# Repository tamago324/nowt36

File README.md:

# nowt36

以下の特徴を持ったキーボードです。

* 自然と手が置ける配列
* 一体型だけど分割型
* 片手5列
* ホットスワップ対応
* ミドルアクリルプレート対応 (オプション)
* アンダーグロー対応 (オプション)

## LICENSE

<br />この 作品 は <a rel="license" href="http://creativecommons.org/licenses/by/4.0/">クリエイティブ・コモンズ 表示 4.0 国際 ライセンス</a>の下に提供されています。

> 帰属—適切なクレジットを表示し、ライセンスへのリンクを提供し、変更が行われたかどうかを示す必要があります。

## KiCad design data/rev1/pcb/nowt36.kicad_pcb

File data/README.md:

# data

| ディレクトリ                      | 説明                                                                      |
|-----------------------------------|---------------------------------------------------------------------------|
| `pcb/`                            | メインPCB                                                                 |
| `pcb_promicro_plate/`             | ProMicro保護プレート用 KiCad プロジェクトたち                             |
| `pcb_top_plate/`                  | トッププレート用 KiCad プロジェクト                                       |
| `dxf/`                            | DXFファイル                                                               |
| `svg/`                            | プレートに使用できるSVGファイル                                           |
| `nowt.FCStd`                      | プレートなどのデータを生成するときに使用したFreeCADプロジェクト           |
| `bk_pcb_middle_plate_lower_data/` | ミドルアクリルプレート (下) 作成用 KiCadプロジェクト (発注には使用しない) |

## 発注する場合

### PCB

| パーツ               | 発注時に使用するファイル                                                                       |
|----------------------|------------------------------------------------------------------------------------------------|
| メインPCB            | `pcb/gerber_to_order` 内の対象の業者のzipファイル                                              |
| ProMicro保護プレート | `pcb_promicro_plate/` の中から発注したいプレートの gerber_to_order 内の対象の業者のzipファイル |
| トッププレート       | `pcb_top_plate/gerber_to_order` 内の対象の業者のzipファイル                                    |

### アクリルプレート

#### それぞれのアクリルプレートのデータを自分で加工して、発注する場合

| パーツ                 | ファイル名                   | 備考                                     |
|------------------------|------------------------------|------------------------------------------|
| ボトムプレート         | `svg/bottom.svg`             |                                          |
| ミドルプレート (上)    | `svg/middle_upper.svg`       |                                          |
| ミドルプレート (下)    | `svg/middle_lower.svg.svg`   |                                          |
| ミドルプレート (上) 左 | `svg/middle_upper_left.svg`  | ミドルプレート (上) を左右で分割したもの |
| ミドルプレート (上) 右 | `svg/middle_upper_right.svg` | ミドルプレート (上) を左右で分割したもの |

ミドルプレート (上) 左、ミドルプレート (上) 右 は、A4サイズの中に「ミドルプレート (下)」、「ミドルプレート (上) 右」、「ミドルプレート (上) 左」 を含めたいときに使用できます。

#### Elecrow などにすべてのアクリルプレートを発注する場合 (DXFファイル)

| パーツ                                                                  | ファイル名                            |
|-------------------------------------------------------------------------|---------------------------------------|
| ボトムプレート、ミドルプレート (上)、ミドルプレート (下) を含んだデータ | `dxf/313x255_bottom_middle_plate.dxf` |

### シリコンカットシート

| パーツ                 | ファイル名                  |
|------------------------|-----------------------------|
| シリコンカット用シート | `svg/silicon_cut_sheet.svg` |

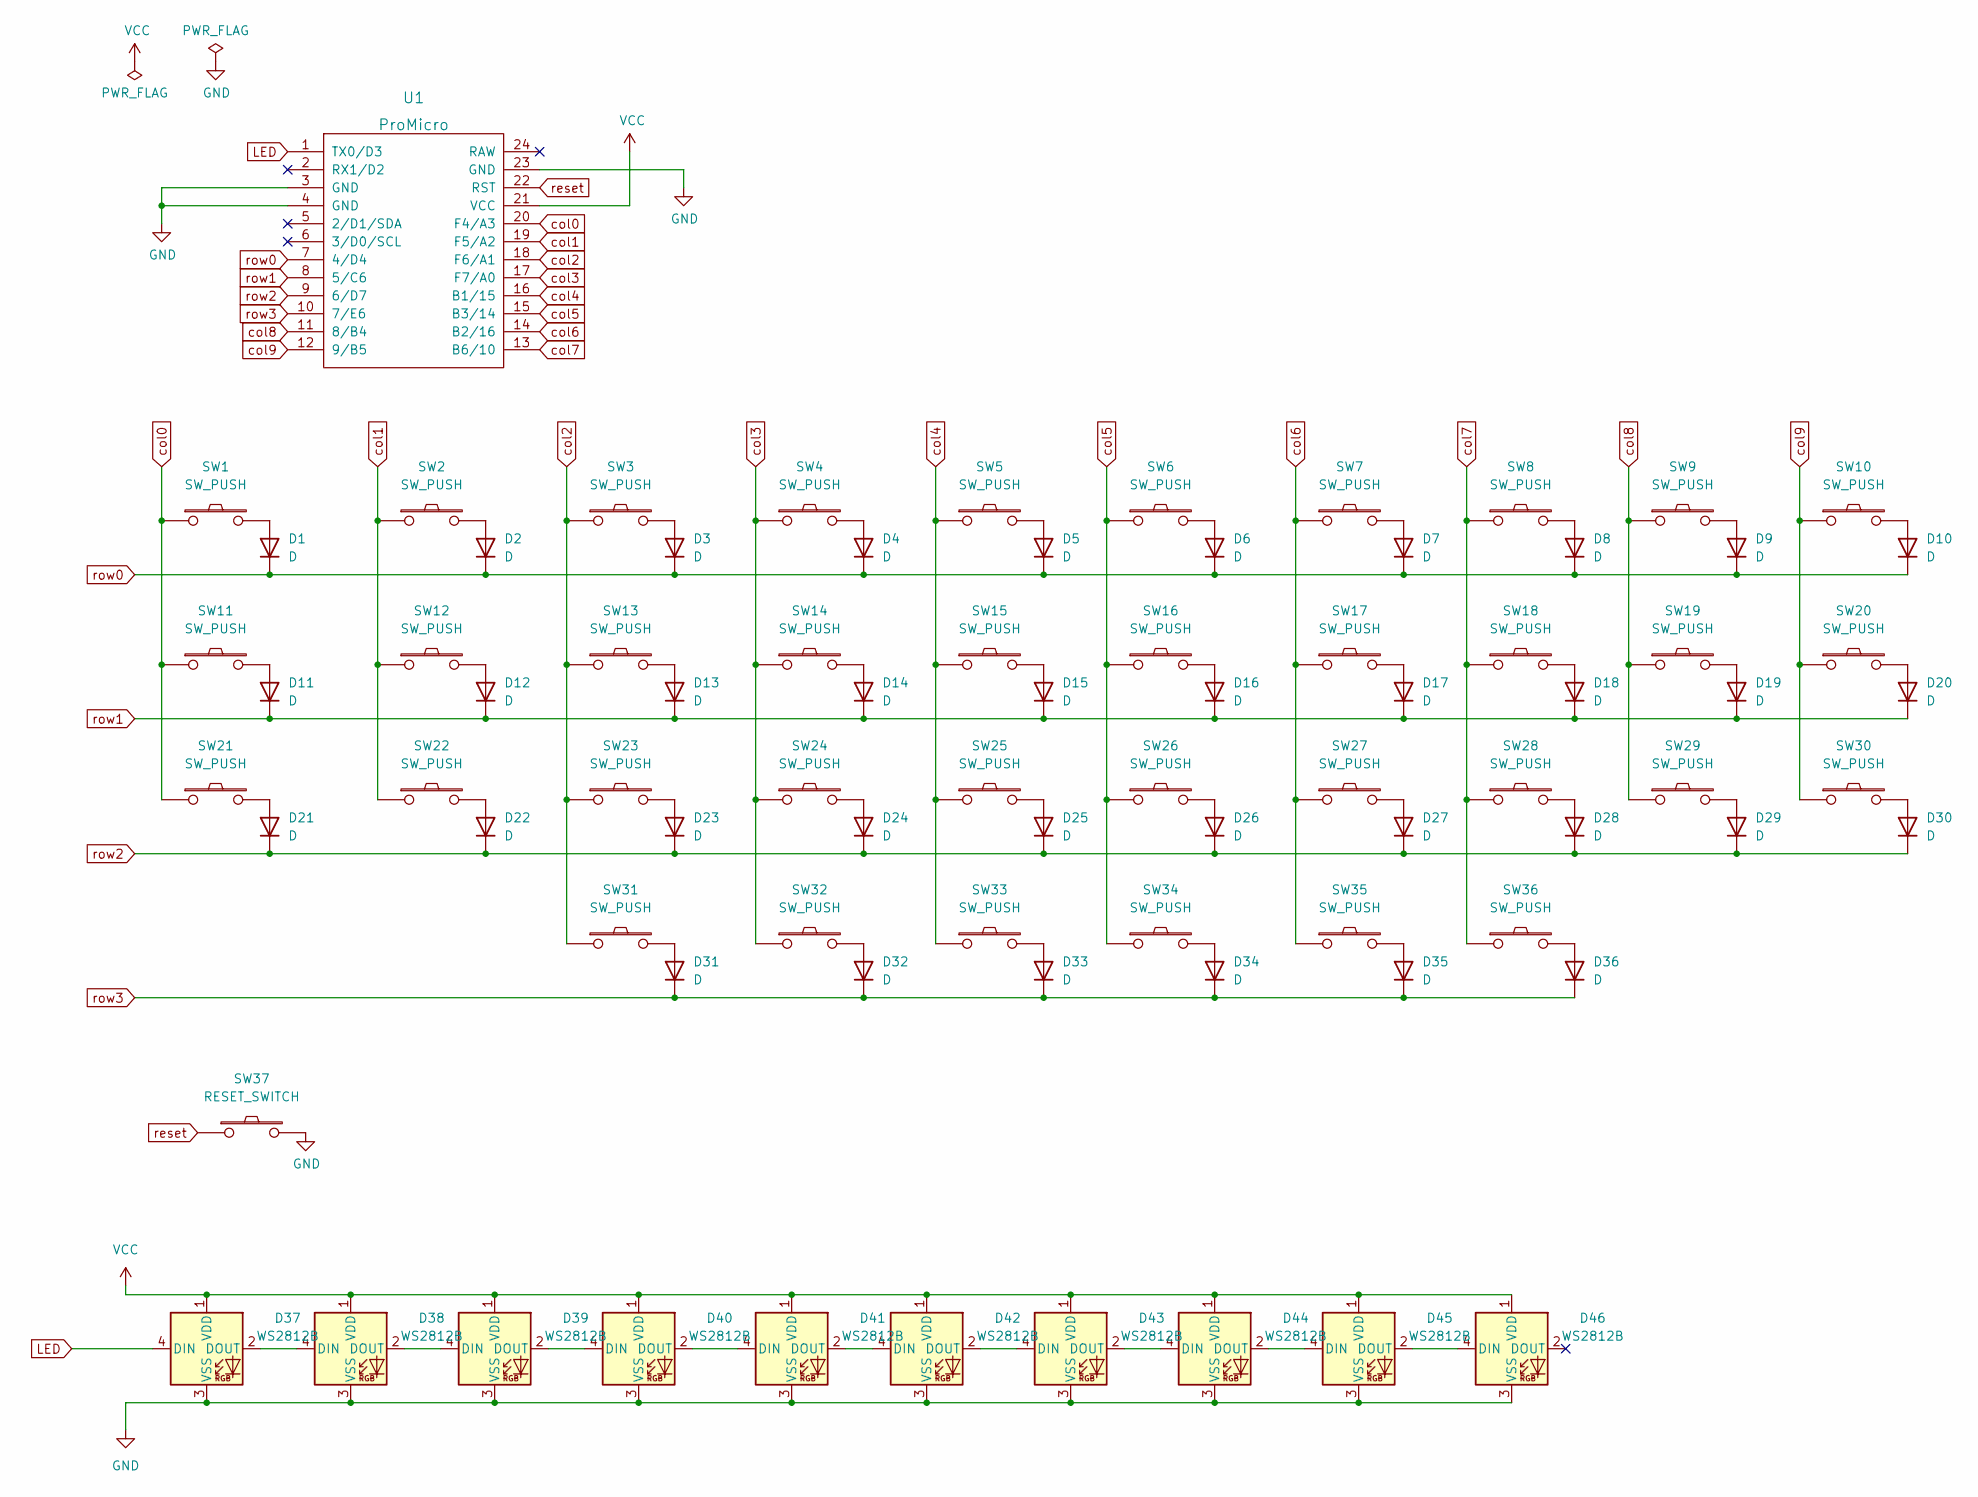
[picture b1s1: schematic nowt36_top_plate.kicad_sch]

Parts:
D1, D2, D3, D4, D5, D6, D7, D8, D9, D10, D11, D12, D13, D14, D15, D16, D17, D18, D19, D20, D21, D22, D23, D24, D25, D26, D27, D28, D29, D30, D31, D32, D33, D34, D35, D36: D; Diode_SMD
D37, D38, D39, D40, D41, D42, D43, D44, D45, D46: WS2812B; LED_WS2812B_PLCC4_5.0x5.0mm_P3.2mm_Back
SW1, SW2, SW3, SW4, SW5, SW6, SW7, SW8, SW9, SW10, SW11, SW12, SW13, SW14, SW15, SW16, SW17, SW18, SW19, SW20, SW21, SW22, SW23, SW24, SW25, SW26, SW27, SW28, SW29, SW30, SW31, SW32, SW33, SW34, SW35, SW36: SW_PUSH; CherryMX_Hotswap
SW37: RESET_SWITCH; ResetSW_1side_back
U1: ProMicro; ProMicro_v3.5_mods

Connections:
GND: D37.3 (VSS), D38.3 (VSS), D39.3 (VSS), D40.3 (VSS), D41.3 (VSS), D42.3 (VSS), D43.3 (VSS), D44.3 (VSS), D45.3 (VSS), D46.3 (VSS), SW37.2, U1.3 (GND), U1.4 (GND), U1.23 (GND)
LED: D37.4 (DIN), U1.1 (TX0/D3)
unnamed: D1.2 (A), SW1.2
unnamed: D2.2 (A), SW2.2
unnamed: D3.2 (A), SW3.2
unnamed: D4.2 (A), SW4.2
unnamed: D5.2 (A), SW5.2
unnamed: D6.2 (A), SW6.2
unnamed: D7.2 (A), SW7.2
unnamed: D8.2 (A), SW8.2
unnamed: D9.2 (A), SW9.2
unnamed: D10.2 (A), SW10.2
unnamed: D11.2 (A), SW11.2
unnamed: D12.2 (A), SW12.2
unnamed: D13.2 (A), SW13.2
unnamed: D14.2 (A), SW14.2
unnamed: D15.2 (A), SW15.2
unnamed: D16.2 (A), SW16.2
unnamed: D17.2 (A), SW17.2
unnamed: D18.2 (A), SW18.2
unnamed: D19.2 (A), SW19.2
unnamed: D20.2 (A), SW20.2
unnamed: D21.2 (A), SW21.2
unnamed: D22.2 (A), SW22.2
unnamed: D23.2 (A), SW23.2
unnamed: D24.2 (A), SW24.2
unnamed: D25.2 (A), SW25.2
unnamed: D26.2 (A), SW26.2
unnamed: D27.2 (A), SW27.2
unnamed: D28.2 (A), SW28.2
unnamed: D29.2 (A), SW29.2
unnamed: D30.2 (A), SW30.2
unnamed: D31.2 (A), SW31.2
unnamed: D32.2 (A), SW32.2
unnamed: D33.2 (A), SW33.2
unnamed: D34.2 (A), SW34.2
unnamed: D35.2 (A), SW35.2
unnamed: D36.2 (A), SW36.2
unnamed: D37.2 (DOUT), D38.4 (DIN)
unnamed: D38.2 (DOUT), D39.4 (DIN)
unnamed: D39.2 (DOUT), D40.4 (DIN)
unnamed: D40.2 (DOUT), D41.4 (DIN)
unnamed: D41.2 (DOUT), D42.4 (DIN)
unnamed: D42.2 (DOUT), D43.4 (DIN)
unnamed: D43.2 (DOUT), D44.4 (DIN)
unnamed: D44.2 (DOUT), D45.4 (DIN)
unnamed: D45.2 (DOUT), D46.4 (DIN)
VCC: D37.1 (VDD), D38.1 (VDD), D39.1 (VDD), D40.1 (VDD), D41.1 (VDD), D42.1 (VDD), D43.1 (VDD), D44.1 (VDD), D45.1 (VDD), D46.1 (VDD), U1.21 (VCC)
col0: SW1.1, SW11.1, SW21.1, U1.20 (F4/A3)
col1: SW2.1, SW12.1, SW22.1, U1.19 (F5/A2)
col2: SW3.1, SW13.1, SW23.1, SW31.1, U1.18 (F6/A1)
col3: SW4.1, SW14.1, SW24.1, SW32.1, U1.17 (F7/A0)
col4: SW5.1, SW15.1, SW25.1, SW33.1, U1.16 (B1/15)
col5: SW6.1, SW16.1, SW26.1, SW34.1, U1.15 (B3/14)
col6: SW7.1, SW17.1, SW27.1, SW35.1, U1.14 (B2/16)
col7: SW8.1, SW18.1, SW28.1, SW36.1, U1.13 (B6/10)
col8: SW9.1, SW19.1, SW29.1, U1.11 (8/B4)
col9: SW10.1, SW20.1, SW30.1, U1.12 (9/B5)
reset: SW37.1, U1.22 (RST)
row0: D1.1 (K), D2.1 (K), D3.1 (K), D4.1 (K), D5.1 (K), D6.1 (K), D7.1 (K), D8.1 (K), D9.1 (K), D10.1 (K), U1.7 (4/D4)
row1: D11.1 (K), D12.1 (K), D13.1 (K), D14.1 (K), D15.1 (K), D16.1 (K), D17.1 (K), D18.1 (K), D19.1 (K), D20.1 (K), U1.8 (5/C6)
row2: D21.1 (K), D22.1 (K), D23.1 (K), D24.1 (K), D25.1 (K), D26.1 (K), D27.1 (K), D28.1 (K), D29.1 (K), D30.1 (K), U1.9 (6/D7)
row3: D31.1 (K), D32.1 (K), D33.1 (K), D34.1 (K), D35.1 (K), D36.1 (K), U1.10 (7/E6)

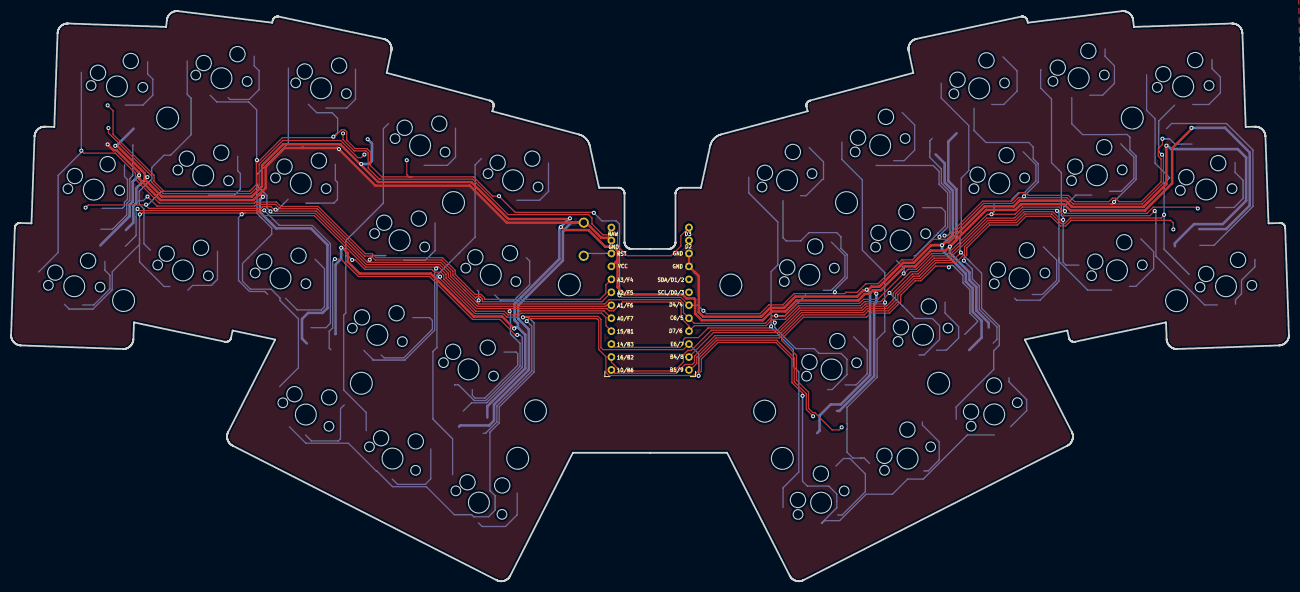
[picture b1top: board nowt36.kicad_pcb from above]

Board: 2 copper layers, 250.7 x 111.8 mm, 98 parts (0 on the bottom side), 63 nets.

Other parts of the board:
HOLE1, HOLE2, HOLE3, HOLE4, HOLE5, HOLE6, HOLE7, HOLE8, HOLE9, HOLE10, HOLE11, HOLE12, HOLE13, HOLE14: Val**; M2_HOLE_v2_4.3mm

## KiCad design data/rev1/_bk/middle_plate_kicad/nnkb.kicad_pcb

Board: 2 copper layers, 48 parts (0 on the bottom side), 10 nets, no tracks yet.

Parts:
D37, D38, D39, D40, D41, D42, D43, D44, D45, D46: WS2812B; LED_WS2812B_PLCC4_5.0x5.0mm_P3.2mm_middle
SW1, SW2, SW3, SW4, SW5, SW6, SW7, SW8, SW9, SW10, SW11, SW12, SW13, SW14, SW15, SW16, SW17, SW18, SW19, SW20, SW21, SW22, SW23, SW24, SW25, SW26, SW27, SW28, SW29, SW30, SW31, SW32, SW33, SW34, SW35, SW36: SW_PUSH; CherryMX_Hotswap_middle
SW37: RESET_SWITCH; ResetSW_1side_back_middle
U1: ProMicro; ProMicro_v3.5_mods_middle

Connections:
col0: SW1.1, SW11.1, SW21.1
col1: SW2.1, SW12.1, SW22.1
col2: SW3.1, SW13.1, SW23.1, SW31.1
col3: SW4.1, SW14.1, SW24.1, SW32.1
col4: SW5.1, SW15.1, SW25.1, SW33.1
col5: SW6.1, SW16.1, SW26.1, SW34.1
col6: SW7.1, SW17.1, SW27.1, SW35.1
col7: SW8.1, SW18.1, SW28.1, SW36.1
col8: SW9.1, SW19.1, SW29.1
col9: SW10.1, SW20.1, SW30.1

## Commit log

2022-07-16 init
2022-07-16 ビルドガイドを修正
2022-07-16 docs: README を更新
2022-07-16 docs: add LICENSE
2022-07-17 シリコンカットサポートシートを追加
2022-07-17 fix typo
2022-07-17 update docs
2022-07-18 ビルドガイド更新
2022-07-18 ビルドガイド修正
2022-07-20 middle upper 修正
2022-07-24 遊舎工房用のデータを追加した
2022-07-31 rev0.7.6 に移動
2022-07-31 rev1 を追加
2022-08-28 rev0.7.6を削除
2022-08-28 ビルドガイドを追加
2022-08-28 データの配置ヲ修正
2022-08-28 Remap でのファームウェアの書き込みに対応
2022-08-28 fix リンクを修正
2022-08-28 シリコンシートカットの画像を追加、修正
2022-08-28 ミドルプレートのzipをダウンロードできるように修正
2022-08-29 画像を修正
2022-08-29 なぜか画像の反映がされないため、ちょっと修正
2022-09-03 ライセンスを CC BY に変更
2022-09-03 不要なデータを削除
2022-09-09 遊舎工房のミドルプレートのリンクを更新
2022-09-14 画像の追加
2022-09-14 画像変更

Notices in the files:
README.md:
CC BY 4.0
